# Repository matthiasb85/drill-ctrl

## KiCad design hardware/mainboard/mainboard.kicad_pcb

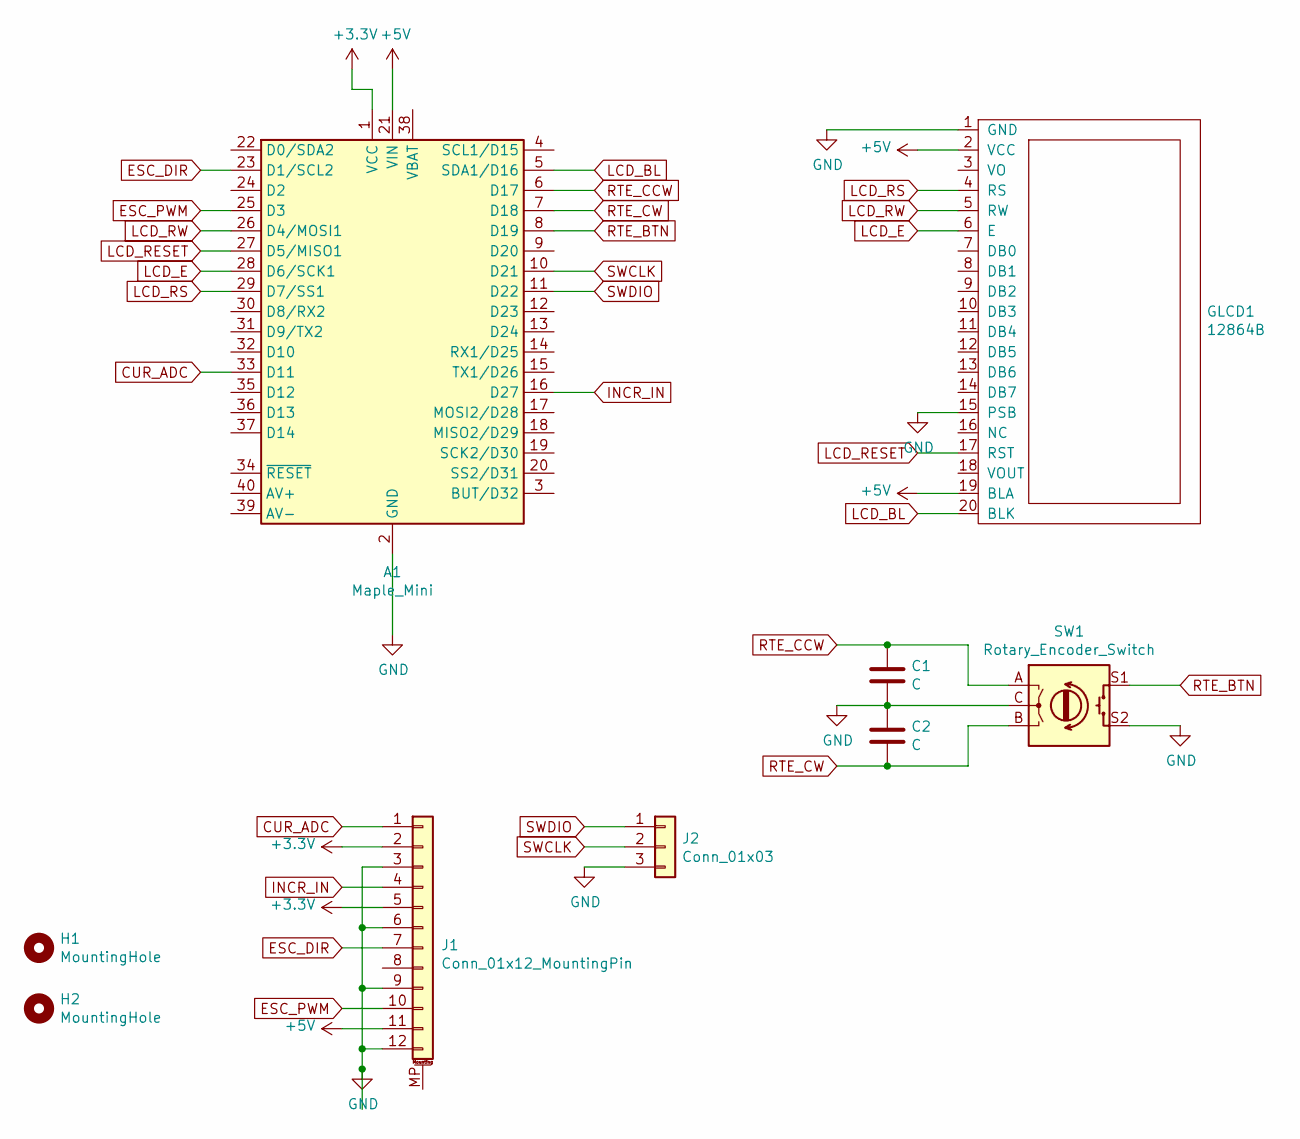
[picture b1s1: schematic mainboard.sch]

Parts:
A1: Maple_Mini
C1, C2: C; C_0603_1608Metric_Pad1.05x0.95mm_HandSolder
GLCD1: 12864B
H1: MountingHole; MountingHole_2.7mm_M2.5_DIN965_Pad
H2: MountingHole; MountingHole_3.2mm_M3
J1: Conn_01x12_MountingPin; PinHeader_1x12_P2.54mm_Horizontal
J2: Conn_01x03; PinHeader_1x03_P2.54mm_Horizontal
SW1: Rotary_Encoder_Switch; RotaryEncoder_Alps_EC11E-Switch_Vertical_H20mm

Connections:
+3V3: A1.1 (VCC), J1.2, J1.5
+5V: A1.21 (VIN), GLCD1.2 (VCC), GLCD1.19 (BLA), J1.11
CUR_ADC: A1.33 (D11), J1.1
ESC_DIR: A1.23 (D1/SCL2), J1.7
ESC_PWM: A1.25 (D3), J1.10
GND: A1.2 (GND), C1.1, C2.2, GLCD1.1 (GND), GLCD1.15 (PSB), J1.3, J1.6, J1.9, J1.12, J2.3, SW1.C, SW1.S2
INCR_IN: A1.16 (D27), J1.4
LCD_BL: A1.5 (SDA1/D16), GLCD1.20 (BLK)
LCD_E: A1.28 (D6/SCK1), GLCD1.6 (E)
LCD_RESET: A1.27 (D5/MISO1), GLCD1.17 (RST)
LCD_RS: A1.29 (D7/SS1), GLCD1.4 (RS)
LCD_RW: A1.26 (D4/MOSI1), GLCD1.5 (RW)
RTE_BTN: A1.8 (D19), SW1.S1
RTE_CCW: A1.6 (D17), C1.2, SW1.A
RTE_CW: A1.7 (D18), C2.1, SW1.B
SWCLK: A1.10 (D21), J2.2
SWDIO: A1.11 (D22), J2.1

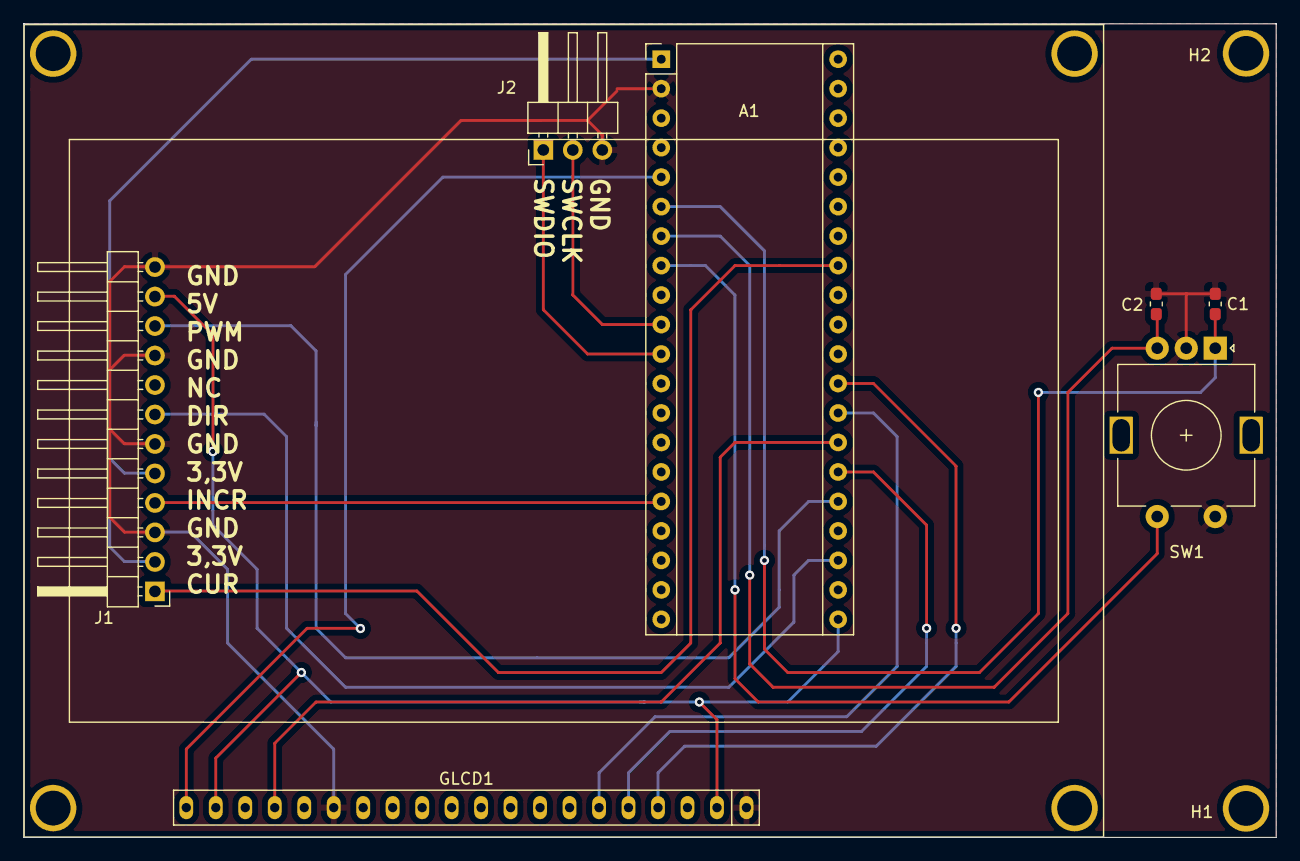
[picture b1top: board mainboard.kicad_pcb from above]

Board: 4 copper layers, 107.9 x 70.1 mm, 9 parts (0 on the bottom side), 17 nets.

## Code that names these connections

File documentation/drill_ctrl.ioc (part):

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Mcu.Name=STM32F103C(8-B)Tx
Mcu.Package=LQFP48
Mcu.UserName=STM32F103CBTx
PA0-WKUP.GPIOParameters=GPIO_Label
PA0-WKUP.GPIO_Label=CUR_ADC
PA0-WKUP.Signal=ADCx_IN0
PA11.Mode=Device
PA11.Signal=USB_DM
PA12.Mode=Device
PA12.Signal=USB_DP
PA13.Mode=Serial_Wire
PA13.Signal=SYS_JTMS-SWDIO
PA14.Mode=Serial_Wire
PA14.Signal=SYS_JTCK-SWCLK
PA4.GPIOParameters=GPIO_Label
PA4.GPIO_Label=LCD_RS
PA4.Mode=NSS_Signal_Hard_Input
PA4.Signal=SPI1_NSS
PA5.GPIOParameters=GPIO_Label
PA5.GPIO_Label=LCD_E
PA5.Mode=TX_Only_Simplex_Unidirect_Master
PA5.Signal=SPI1_SCK
PA6.GPIOParameters=GPIO_Label
PA6.GPIO_Label=LCD_RESET
PA6.Signal=GPIO_Output
PA7.GPIOParameters=GPIO_Label
PA7.GPIO_Label=LCD_RW
PA7.Mode=TX_Only_Simplex_Unidirect_Master
PA7.Signal=SPI1_MOSI
PA8.GPIOParameters=GPIO_Label
PA8.GPIO_Label=INCR_IN
PA8.Signal=S_TIM1_CH1
PB0.GPIOParameters=GPIO_Label
PB0.GPIO_Label=ESC_PWM
PB0.Signal=S_TIM3_CH3
PB10.GPIOParameters=GPIO_Label
PB10.GPIO_Label=ESC_DIR
PB10.Signal=GPIO_Output
PB3.GPIOParameters=GPIO_Label
PB3.GPIO_Label=BTN
PB3.Signal=GPXTI3
PB4.GPIOParameters=GPIO_Label
PB4.GPIO_Label=CW
PB4.Signal=GPXTI4
PB5.GPIOParameters=GPIO_Label
PB5.GPIO_Label=CCW
PB5.Signal=GPXTI5
PB6.GPIOParameters=GPIO_Label
PB6.GPIO_Label=LCD_BL
PB6.Signal=S_TIM4_CH1
PD0-OSC_IN.Mode=HSE-External-Oscillator
PD0-OSC_IN.Signal=RCC_OSC_IN
PD1-OSC_OUT.Mode=HSE-External-Oscillator
PD1-OSC_OUT.Signal=RCC_OSC_OUT

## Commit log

2020-03-20 created skeleton
2020-03-20 added eclipse project files
2020-04-16 folder changed structure for chibios files
2020-04-16 added STM32Cube project for documentation purpose
2020-04-16 worked on structure
2020-04-16 added placeholder files
2020-04-16 added first working version of rotary encoder driver
2020-04-16 removed obsolete SDU1
2020-04-20 added first version of revolution counter, driver is not working yet
2020-04-22 first version of revolution counter working
2020-04-22 code cleanup
2020-04-25 pwm driver working, read function currently broken
2020-04-26 fixed merge fuckup
2020-04-26 fixed esc_read function
2020-04-26 added peripheral view properties (project type and configuration entry) to Eclipse project files
2020-05-06 fixed pin mapping
2020-05-06 added dependency to u8g2
2020-05-06 first working version with u8g2 based glcd interface
2020-05-08 added license file
2020-05-18 massive software restructuring, glcd driver breaks reolution counter
2020-05-23 removed obsolete files, added first working menu, added mean for rev_cnt, improved glcd driver
2020-05-23 removed debug pin toggle
2020-05-25 worked on menu, added first simple control loop
2020-05-25 reduzed RAM usage
2020-05-25 fixed race condition in increment encoder
2020-05-26 added direction pin for esc_pwm
2020-06-22 added first version for ADC current readout
2020-07-02 modified current adc driver
2020-07-02 changed pin settings
2020-07-02 fixed calculation in current adc driver
2020-07-02 first schematic and layout version for mainboard
2020-07-11 generated gerber files for jlcpcb
2020-08-03 worked on application, added simple mean value filter
2020-08-03 worked on 3d models for control panel construction
2020-08-03 added 3d model files
2020-08-10 countersunk control knob
2020-08-10 added model with direct tapping into stand of
2020-08-10 modified exported stl files, top is based on version without additional threaded inserts
